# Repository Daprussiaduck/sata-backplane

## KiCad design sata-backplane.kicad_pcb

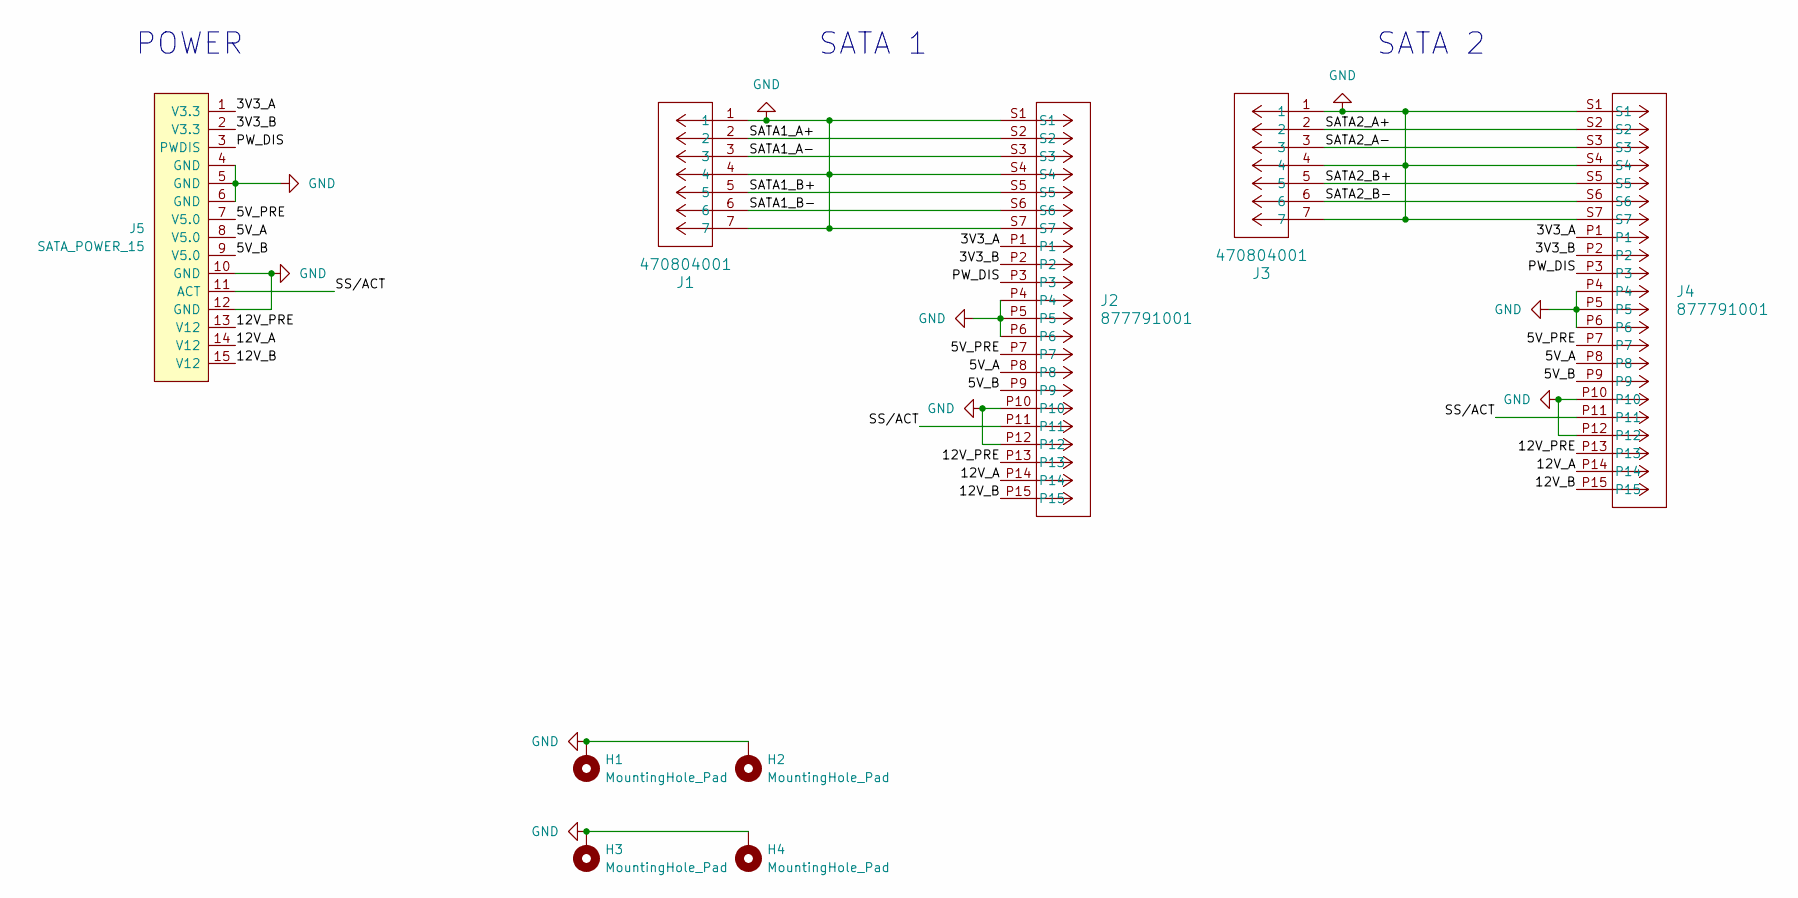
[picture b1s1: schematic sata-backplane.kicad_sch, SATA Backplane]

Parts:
H1, H2, H3, H4: MountingHole_Pad; MountingHole_3.2mm_M3_Pad_TopBottom
J1, J3: 470804001; CONN_47080-4001_MOL
J2, J4: 877791001; CONN_877791001_MOL
J5: SATA_POWER_15; SATA_Power

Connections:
/3V3_A: J2.P1, J4.P1, J5.1 (V3.3)
/3V3_B: J2.P2, J4.P2, J5.2 (V3.3)
/5V_A: J2.P8, J4.P8, J5.8 (V5.0)
/5V_B: J2.P9, J4.P9, J5.9 (V5.0)
/5V_PRE: J2.P7, J4.P7, J5.7 (V5.0)
/12V_A: J2.P14, J4.P14, J5.14 (V12)
/12V_B: J2.P15, J4.P15, J5.15 (V12)
/12V_PRE: J2.P13, J4.P13, J5.13 (V12)
/PW_DIS: J2.P3, J4.P3, J5.3 (PWDIS)
/SATA1_A+: J1.2, J2.S2
/SATA1_A-: J1.3, J2.S3
/SATA1_B+: J1.5, J2.S5
/SATA1_B-: J1.6, J2.S6
/SATA2_A+: J3.2, J4.S2
/SATA2_A-: J3.3, J4.S3
/SATA2_B+: J3.5, J4.S5
/SATA2_B-: J3.6, J4.S6
/SS/ACT: J2.P11, J4.P11, J5.11 (ACT)
GND: H1.1, H2.1, H3.1, H4.1, J1.1, J1.4, J1.7, J2.P4, J2.P5, J2.P6, J2.P10, J2.P12, J2.S1, J2.S4, J2.S7, J3.1, J3.4, J3.7, J4.P4, J4.P5, J4.P6, J4.P10, J4.P12, J4.S1, J4.S4, J4.S7, J5.4 (GND), J5.5 (GND), J5.6 (GND), J5.10 (GND), J5.12 (GND)

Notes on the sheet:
SATA 1
SATA 2
POWER

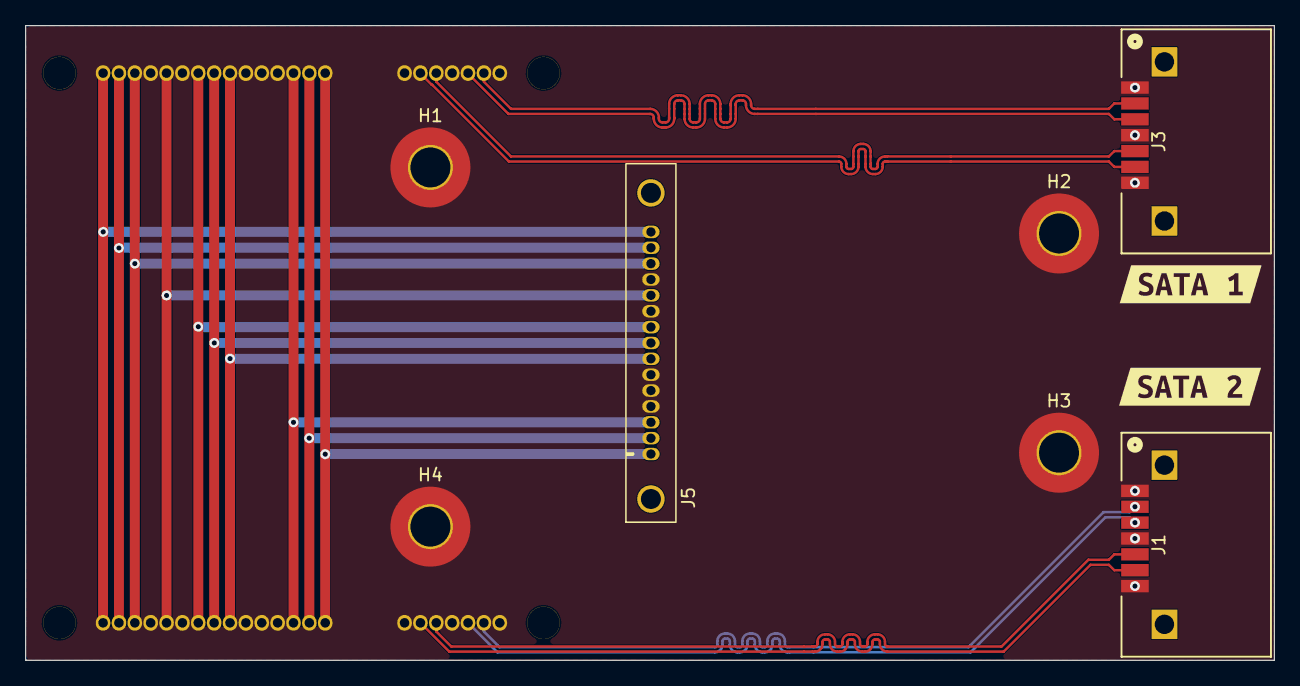
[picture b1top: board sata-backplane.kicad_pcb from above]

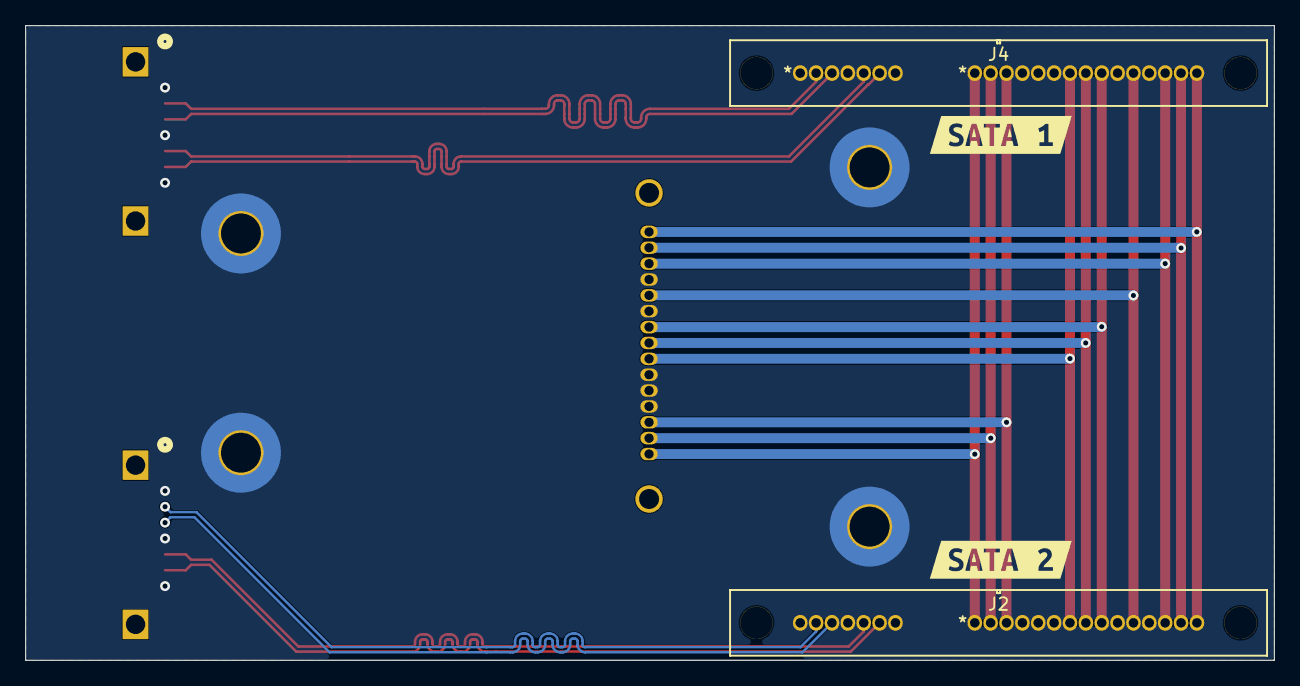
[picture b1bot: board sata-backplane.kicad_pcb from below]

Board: 2 copper layers, 100.0 x 50.8 mm, 13 parts (4 on the bottom side), 19 nets.

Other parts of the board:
kibuzzard-63B1B17B, kibuzzard-63B1B17B#2: G***; kibuzzard-63B1B17B
kibuzzard-63B1B175, kibuzzard-63B1B175#2: G***; kibuzzard-63B1B175

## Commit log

2026-01-18 Modified PCB to fit the AX700 Drive Cages
2026-02-22 Done, New parts & spacing
2026-02-23 DRC foxes for PCBway
2026-03-13 Completed - 3D model
2026-04-08 more relief for Exos drives
2026-04-08 remove history folder

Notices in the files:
sata-backplane.kicad_sch:
GPL v3
